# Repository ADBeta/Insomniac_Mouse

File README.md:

# Insomniac Mouse MkII
USB HID Mouse Device using a 10¢ Microcontroller.  
Moves randomly to keep PCs awake; make games harder to play; annoy co-workers 
and friends; or to give you a digital fishbowl to watch.  
Each board has jumpers to change the Mouse Behaviour, a lanyard loop,
and is designed with minimum cost and complexity.

Using [ch32v003fun](https://github.com/cnlohr/ch32v003fun) and 
[rv003usb](https://github.com/cnlohr/rv003usb) to create a Software Defined
HID Mouse - it then uses `Bresenham's Line Algorithm` to plot lines for the
mouse to move.

<div style="display: flex; align-items: center; gap: 10px;">
  <br>
  <br>

</div>

## Jumpers

|    Mode    | J1  | J2  | J3  |        Description        |                             Usecase                       |
|------------|-----|-----|-----|---------------------------|-----------------------------------------------------------|
|   Normal   |  0  |  0  |  0  |    ±125 Units Movement    |           Default balance of speed and distance           |
|   Hi-Res   |  1  |  0  |  0  |    ±250 Units Movement    |            Longer movement for Hi DPI Displays            |
|   Jitter   |  0  |  1  |  0  |     ±20 Units Movement    |    More chaotic movement. Good for messing with games     |
|   Stepped  |  1  |  1  |  0  | ±2 Unit Movement (Slower) |     Slow mode for controllability while plugged in        |
|   Square   |  0  |  0  |  1  | Lock movement to a square |         Prevents the mouse from wandering too far         |
|   Unused   |  1  |  0  |  1  |                           |                                                           |
|   Unused   |  0  |  1  |  1  |                           |                                                           |
|   Unused   |  1  |  1  |  1  |                           |                                                           |

## Uses
### Keeping PCs awake
Even if you disable Screensaver/Sleep mode, some PCs go to sleep anyway - 
this forces the machine to stay awake regardless.  
This is especially useful on Industial, Unmanaged and headless machines.

### Testing USB Ports
Due to the very low power consumption, small size, lanyard loop, USB 1.0
connection spec, and simple HID data, this is a perfect cheap USB Tester.

### Activity Monitor Spoofing
Because this moves the mouse like any other HID Mouse, it keeps users as
`"Online"` on Teams, Slack etc programs which monitor user activity.  
**WARNING This is not recommended, and any touble you get into for doing this
is your own fault.**

### Pranks / Game Challenges
Guaranteed to annoy your friends and make games **much** harder to play.  

### Creating Artwork
Hold down the mouse in an art package of your choice to create 
some.... interesting art.  
<div style="display: flex; align-items: center; gap: 10px;">
  <br>
  <br>
  <br>
</div>

## PCB Specification
The overall thickness of the PCBs **MUST** be between 2.0mm and 2.4mm.  
`MkII` Offers more adaptability to get to this final thickness easily.
* Order `Insomniac_USB_Gerb` as a 2.0mm PCB
* Order `Insomniac_USB_Gerb` as a 1.6mm PCB and glue on a 0.4mm - 0.8mm Shim
* Order `Insomniac_USB_Gerb` and `Insomniac_Shim_Gerb` as 1.2mm or 1.0mm PCBs and glue together

## Partslist
```
U1    CH32V003J4M6       SOIC-8
U2    AP2112K-3.3        SOT-23-5
C1    100nF MLCC         0603
C2    100nF MLCC         0603
R1    1.5K Ohm           0603
```

## CHANGELOG
* V1.0.1 - Fixed a compatability issue with Windows
* V1.1.2 - Refactor functions and vairable names
* V1.2.0 - Added Diagonal Movement for USB HID Data, improves smoothness
* V1.3.2 - Changed Jumper Detection Method & added `JITTER` Mode
* V1.4.0 - Refined the code and added `CALM` Mode.
* V1.5.0 - Added USB Serial Number based on UUID of the MCU
* V2.0.0 - MkII PCB and minor bug fixes & refactor
* V2.1.0 - Added Square Limit Mode

## TODO

----
MIT License
Copyright (c) 2025-2026 ADBeta

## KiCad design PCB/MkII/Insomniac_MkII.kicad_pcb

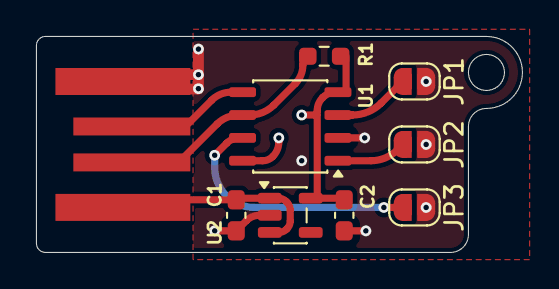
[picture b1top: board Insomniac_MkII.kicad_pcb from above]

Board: 2 copper layers, 27.0 x 12.0 mm, 10 parts (1 on the bottom side), 9 nets.

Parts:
C1, C2: 100nF; C_0603_1608Metric_Pad1.08x0.95mm_HandSolder
J1: PCB_USB; PCB_USB_A
J2: CONN_PROG; Program_Conn
JP1: JP1; SolderJumper-2_P1.3mm_Open_RoundedPad1.0x1.5mm
JP2: JP2; SolderJumper-2_P1.3mm_Open_RoundedPad1.0x1.5mm
JP3: JP3; SolderJumper-2_P1.3mm_Open_RoundedPad1.0x1.5mm
R1: 1K5; R_0603_1608Metric_Pad0.98x0.95mm_HandSolder
U1: CH32V003JxMx; JEITA_SOIC-8_3.9x4.9mm_P1.27mm
U2: AP2112K-3.3; SOT-23-5

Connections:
/JP1: JP1.1 (A), U1.3 (PA2)
/JP2: JP2.1 (A), U1.1 (PD6/PA1)
/JP3: JP3.1 (A), U1.7 (PC4)
/SWIO: J2.3, U1.8 (PD1/PD4/PD5)
/USB_D+: J1.3 (D+), U1.5 (PC1)
/USB_D-: J1.2 (D-), R1.1, U1.6 (PC2)
/VBUS_3V3: C2.1, J2.2, R1.2, U1.4 (VDD), U2.5 (VOUT)
GND: C1.2, C2.2, J1.4 (GND), J2.1, J2.4, JP1.2 (B), JP2.2 (B), JP3.2 (B), U1.2 (VSS), U2.2 (GND)
unnamed: C1.1, J1.1 (VBUS), U2.1 (VIN), U2.3 (EN)

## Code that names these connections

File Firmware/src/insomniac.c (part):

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* See the GitHub: https://github.com/ADBeta/Insomniac_Mouse
*
* Pinout:
* 	USB+   PC1
* 	USB-   PC2
* 	JP1    PA2
* 	JP2    PA1
* 	JP3    PC4
*
* ADBeta (c) 2025-2026    02 Jun 2026    Ver2.1.0
******************************************************************************/
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	// Enable the GPIO Channels
	RCC->APB2PCENR |= RCC_APB2Periph_GPIOA | RCC_APB2Periph_GPIOC;

	// Clear PA1 PA2 and PC4, set them to Push/Pull, then write PULLUP
	GPIOA->CFGLR &= ~((0x0000000F << 4) | (0x0000000F << 8));
	GPIOA->CFGLR |=  ((GPIO_CFGLR_IN_PUPD << 4) | (GPIO_CFGLR_IN_PUPD << 8));
	GPIOA->OUTDR |=  ((0x01 << 1) | (0x01 << 2));
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	GPIOC->OUTDR |=  (0x01 << 4);

	// Read the Jumpers to set the user_mode
	g_user_mode |= (!((GPIOA->INDR >> 2) & 1)) << 0;  // PA2
	g_user_mode |= (!((GPIOA->INDR >> 1) & 1)) << 1;  // PA1
	g_user_mode |= (!((GPIOC->INDR >> 4) & 1)) << 2;  // PC4


	/*** USB ****************************/
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
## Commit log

2025-01-09 Changed to integer position system
2025-01-10 Converted to Co-ordinate system
2025-01-10 Added Ring Buffer
2025-01-11 Code functional. Needs tuning
2025-01-11 Fine-tuning for unbiased rand()
2025-01-11 Firmware Ver 1.0 Finished. Sets random seed based on RAM, tunes to be well biased
2025-01-11 Updated Averagr Script. Added gitignore
2025-01-11 Testing
2025-01-11 Fixed gitignore
2025-01-11 Removed build dir
2025-01-11 Stop tracking build directory
2025-01-12 Added min/max outputs
2025-01-12 Fixed compat issue with Windows
2025-01-12 V1.0.1
2025-01-12 PCB Finished
2025-01-13 Starting pattern concept
2025-01-13 Added Jumper Handling
2025-01-14 V1.1.0
2025-01-18 Added peek and skip buffer functions for use later
2025-01-19 refactor delta to instruction
2025-01-20 Added Images
2025-01-20 Added Diagonal Movement. Needs Testing
2025-01-20 Added demo artwork
2025-01-20 V1.2.0
2025-02-17 Layout for Jumper Modes
2025-02-17 Added TODO
2025-02-18 Started adding user modes
2025-02-18 Changed HI_RES units
2025-02-20 V1.3.2
2025-02-20 Fixed mode selection
2025-02-21 Changed Serial No. to 8 char. Testing Multi-device support
2026-02-12 V1.4.0 Calm Mode Test
2026-02-12 Slowed down calm mode
2026-02-13 V1.5.0 UUID Based iSerial
2026-02-14 MkII HW & FW
2026-06-01 V2.0.1 - Testing a limited box mode
2026-06-02 V2.1.0 Released
